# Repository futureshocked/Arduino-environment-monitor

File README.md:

# Arduino-environment-monitor
This repository contains code and schematics for our course Arduino Environment Monitor

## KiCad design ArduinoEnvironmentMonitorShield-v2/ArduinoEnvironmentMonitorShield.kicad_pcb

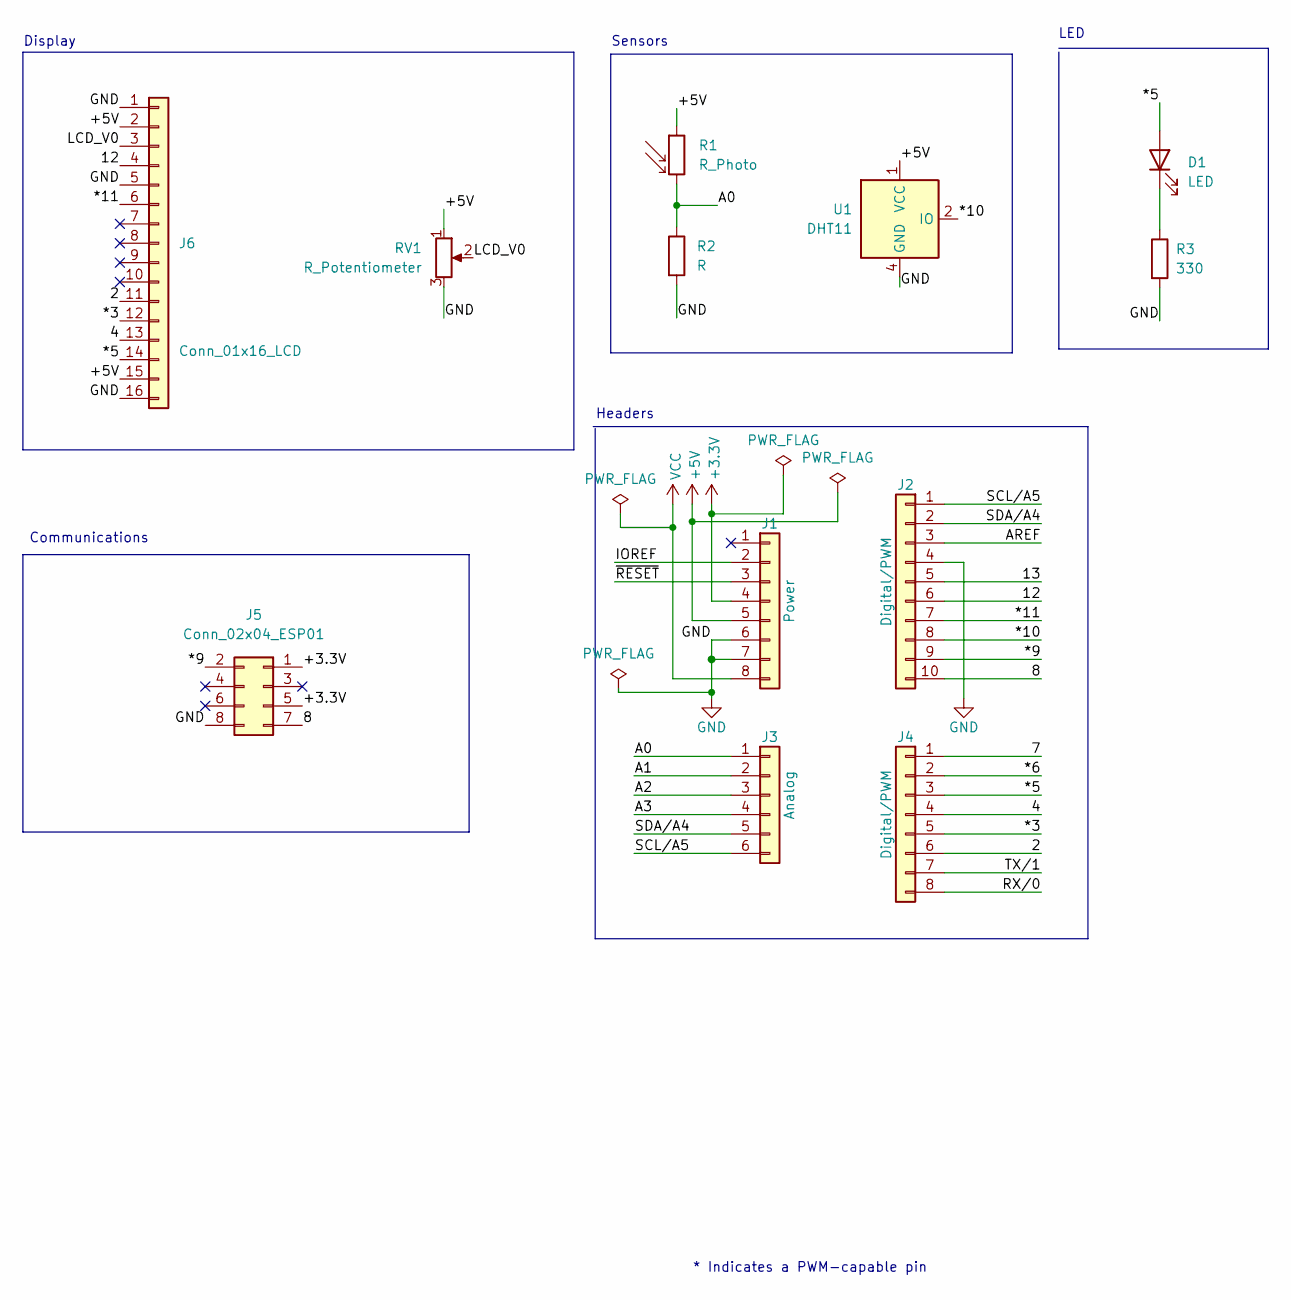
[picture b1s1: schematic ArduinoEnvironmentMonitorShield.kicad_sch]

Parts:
D1: LED; LED_D3.0mm
J1: Power; PinSocket_1x08_P2.54mm_Vertical
J2: Digital/PWM; PinSocket_1x10_P2.54mm_Vertical
J3: Analog; PinSocket_1x06_P2.54mm_Vertical
J4: Digital/PWM; PinSocket_1x08_P2.54mm_Vertical
J5: Conn_02x04_ESP01; PinSocket_2x04_P2.54mm_Vertical
J6: Conn_01x16_LCD; PinHeader_1x16_P2.54mm_Vertical
R1: R_Photo; R_Axial_DIN0204_L3.6mm_D1.6mm_P1.90mm_Vertical
R2: R; R_Axial_DIN0207_L6.3mm_D2.5mm_P7.62mm_Horizontal
R3: 330; R_Axial_DIN0207_L6.3mm_D2.5mm_P7.62mm_Horizontal
RV1: R_Potentiometer; Potentiometer_Vishay_T73YP_Vertical
U1: DHT11; Aosong_DHT11_5.5x12.0_P2.54mm

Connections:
+3V3: J1.4
+5V: J1.5, J6.2, J6.15, R1.1, RV1.1, U1.1 (VCC)
/2: J4.6, J6.11
/4: J4.4, J6.13
/7: J4.1
/8: J2.10, J5.7
/12: J2.6, J6.4
/13: J2.5
/*3: J4.5, J6.12
/*5: D1.2 (A), J4.3, J6.14
/*6: J4.2
/*9: J2.9, J5.2
/*10: J2.8, U1.2 (IO)
/*11: J2.7, J6.6
/+3.3V: J5.1, J5.5
/A0: J3.1, R1.2, R2.1
/A1: J3.2
/A2: J3.3
/A3: J3.4
/AREF: J2.3
/IOREF: J1.2
/LCD_V0: J6.3, RV1.2
/RX/0: J4.8
/SCL/A5: J2.1, J3.6
/SDA/A4: J2.2, J3.5
/TX/1: J4.7
/~RESET: J1.3
GND: J1.6, J1.7, J2.4, J5.8, J6.1, J6.5, J6.16, R2.2, R3.2, RV1.3, U1.4 (GND)
unnamed: D1.1 (K), R3.1
VCC: J1.8

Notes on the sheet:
Communications
LED
Headers
* Indicates a PWM-capable pin
Display
Sensors

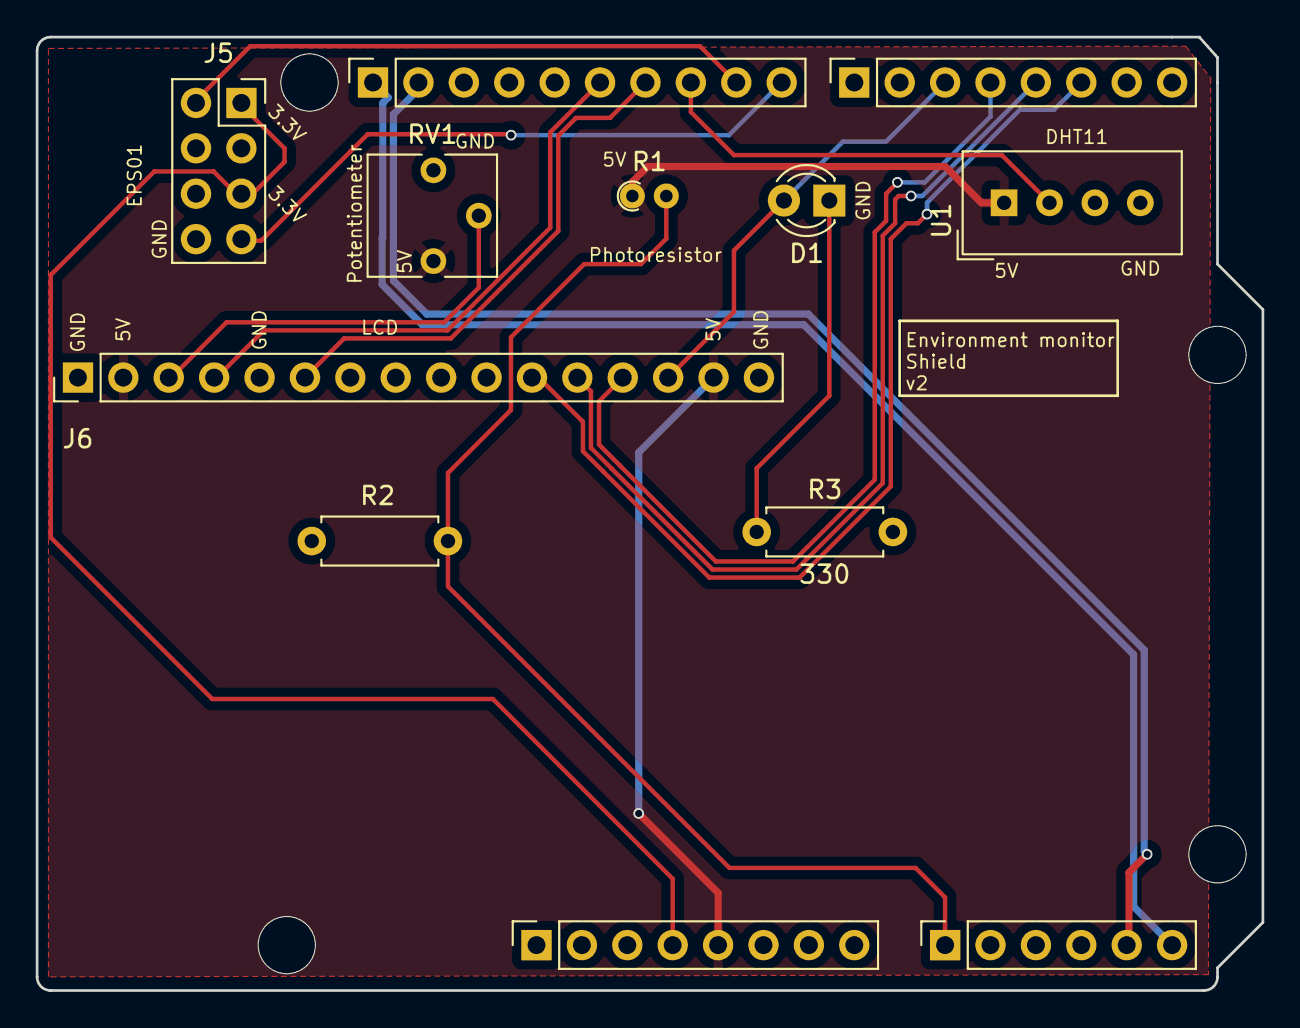
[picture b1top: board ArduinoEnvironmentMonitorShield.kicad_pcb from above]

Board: 2 copper layers, 68.6 x 53.3 mm, 16 parts (0 on the bottom side), 17 nets.

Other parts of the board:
MH1, MH2, MH3, MH4: MountingHole_3.2mm
